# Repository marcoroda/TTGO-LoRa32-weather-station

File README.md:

# ttgo-LoRa-weatherStation
TTGO board hooked up with BME280 and connected to TTN through LoRa.

* /hw : Hardware related (PCB, Schematics, 3D case, etc).
* /src : PlatformIO project.
* /node-RED : node-RED app retrieving LoRa payload from The Things Network

Project documentation [here](https://marcoroda.com/2020/04/12/TTGO-LORA-TTN.html)

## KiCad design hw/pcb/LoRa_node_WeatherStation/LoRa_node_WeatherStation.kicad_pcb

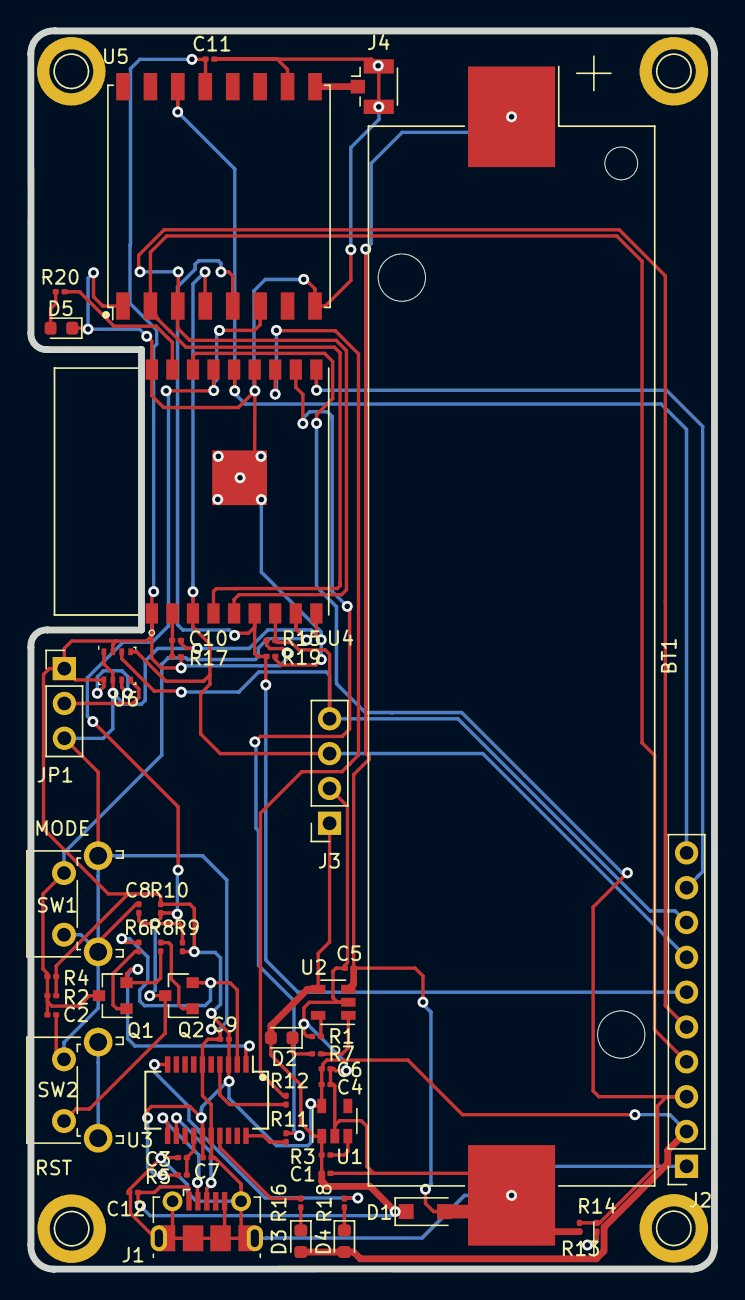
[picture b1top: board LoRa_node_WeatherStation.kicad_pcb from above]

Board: 2 copper layers, 49.9 x 90.3 mm, 53 parts (0 on the bottom side), 38 nets.

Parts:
BT1: Battery_Cell; BatteryHolder_Keystone_1042_1x18650
C1, C4, C5, C9, C11: 10uF; C_0201_0603Metric
C2, C3, C7, C8, C10: 100nF; C_0201_0603Metric
C6: 1uF; C_0201_0603Metric
C12: 0.1uF; C_0201_0603Metric
D1: MBR120; D_SOD-123F
D2: ORANGE_LED; LED_0603_1608Metric
D3, D4: Blue_LED; LED_0603_1608Metric
D5: RED_LED; LED_0603_1608Metric
J1: USB_B_Micro; USB_Micro-B_Molex-105017-0001
J2: Conn_01x10; PinSocket_1x10_P2.54mm_Vertical
J3: BME breakout; PinSocket_1x04_P2.54mm_Vertical
J4: Conn_Coaxial; U.FL_Hirose_U.FL-R-SMT-1_Vertical
JP1: I2C slave Addr; PinHeader_1x03_P2.54mm_Vertical
Q1, Q2: BC848; SOT-23
R1, R2, R4, R5, R6, R8, R9, R10, R13, R14, R15, R17, R19: 10k; R_0201_0603Metric
R3: 100k; R_0201_0603Metric
R7, R16, R18, R20: 1k; R_0201_0603Metric
R11, R12: 470R; R_0201_0603Metric
SW1: MODE; SW_Tactile_SPST_Angled_PTS645Vx83-2LFS
SW2: RST; SW_Tactile_SPST_Angled_PTS645Vx83-2LFS
U1: SPX3819M5-L-3-3; SOT-23-5
U2: MCP73831-2-OT; SOT-23-5
U3: FT231XS; SSOP-20_3.9x8.7mm_P0.635mm
U4: ESP-WROOM-02; MODULE_ESP-WROOM-02
U5: RFM95W-868S2; HOPERF_RFM9XW_SMD
U6: BME280; Bosch_LGA-8_2.5x2.5mm_P0.65mm_ClockwisePinNumbering

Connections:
+BATT: BT1.1, C5.2, D1.2, R13.1, U2.3
/ADC: J2.3, R13.2, R14.1, U4.16
/ANT: J4.1, U5.9
/D+: J1.3, U3.12
/D-: J1.2, U3.11
/DTR: Q1.2, R8.1, U3.1
/IO0: C2.1, Q1.3, R2.1, R4.2, SW1.2, U4.8
/IO4: J2.9, U4.10
/IO16: R20.2, U4.17
/MISO: J2.4, U4.4, U5.2
/MOSI: J2.5, U4.5, U5.3
/RFM95_IRQ: J2.10, U4.14, U5.14
/RFM95_NSS: J2.6, R19.1, U4.6, U5.5
/RST: C8.1, Q2.3, R9.2, R10.1, SW2.1, U4.15, U5.6
/RTS: Q2.2, R6.1, U3.2
/RXD: R12.1, U4.12
/SCK: J2.7, J3.3, U4.3, U5.4, U6.4
/SDA: J2.8, J3.4, R15.2, U4.7, U6.3
/TXD: R11.1, U4.11
GND: BT1.2, C1.1, C2.2, C3.1, C4.1, C5.1, C6.1, C7.1, C8.2, C9.1, C10.2, C11.1, C12.1, D5.1, J1.5, J1.6, J2.1, J3.2, J4.2, JP1.3, R1.2, R14.2, R19.2, SW1.1, SW2.2, U1.2, U2.2, U3.6, U3.16, U4.9, U4.13, U4.18, U4.19, U5.1, U5.8, U5.10, U6.1, U6.7
unnamed: C3.2, R5.2, U3.14
unnamed: C10.1, R17.1, U4.2
unnamed: D2.1, R7.1
unnamed: D3.1, R16.1
unnamed: D4.1, R18.1
unnamed: D5.2, R20.1
unnamed: JP1.2, U6.5
unnamed: Q1.1, R6.2
unnamed: Q2.1, R8.2
unnamed: R1.1, U2.5
unnamed: R3.1, U1.3
unnamed: R7.2, U2.1
unnamed: R11.2, U3.20
unnamed: R12.2, U3.4
unnamed: R16.2, U3.17
unnamed: R18.2, U3.10
VBUS: C1.2, C12.2, D1.1, D2.2, J1.1, J3.1, R3.2, U1.1, U2.4
VDD: C4.2, C6.2, C7.2, C9.2, C11.2, D3.2, D4.2, J2.2, JP1.1, R2.2, R4.1, R5.1, R9.1, R10.2, R15.1, R17.2, U1.5, U3.3, U3.15, U4.1, U5.13, U6.2, U6.6, U6.8

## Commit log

2020-04-06 First commit.
2020-04-06 node-RED app working.
2020-04-06 Added empty LoRa device_config.h (to be filled by user).
2020-04-06 Added info to README.
2020-04-06 Update README.
2020-04-08 Added sensor readings to a fancy Node-Red dashboard.
2020-04-08 Sending dummy sensor values: - Each sensor reading is sent using two bytes; - A message array is constructed with all dummy values (temperature, humidity and pressure)
2020-04-08 Moved Bmeas.h to /include.
2020-04-17 defined com port under Linux
2020-04-18 Updated project doc link.
2020-05-01 First draft PCB.
